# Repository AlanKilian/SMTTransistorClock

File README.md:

# SMTTransistorClock
Project files for a hand-built SMT transistor digital clock.

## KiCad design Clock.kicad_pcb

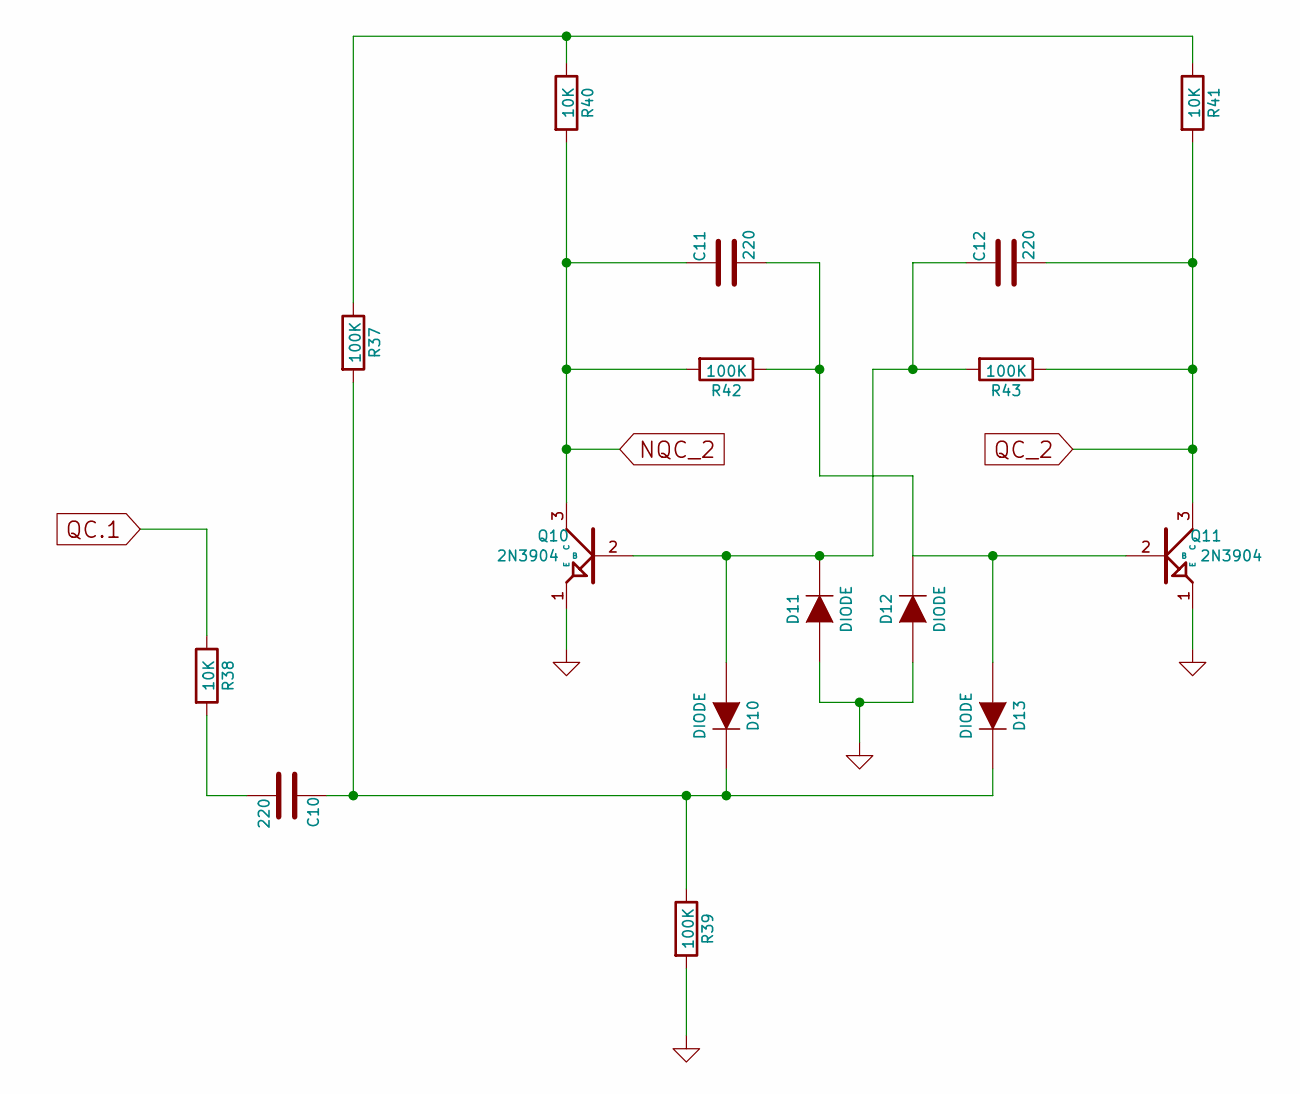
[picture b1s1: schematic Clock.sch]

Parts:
C10, C11, C12: 220; C_0805
D10, D11, D12, D13: DIODE; C_0805
Q10, Q11: 2N3904; sc70
R37, R39, R42, R43: 100K; R_0805
R38, R40, R41: 10K; R_0805

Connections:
GND: D11.1 (A), D12.1 (A), Q10.1 (E), Q11.1 (E), R39.2
NQC_2: C11.1, Q10.3 (C), R40.2, R42.2
unnamed: C10.1, D10.2 (K), D13.2 (K), R37.2, R39.1
unnamed: C10.2, R38.2
unnamed: C11.2, D12.2 (K), D13.1 (A), Q11.2 (B), R42.1
unnamed: C12.1, D10.1 (A), D11.2 (K), Q10.2 (B), R43.2
unnamed: R37.1, R40.1, R41.1
QC.1: R38.1
QC_2: C12.2, Q11.3 (C), R41.2, R43.1

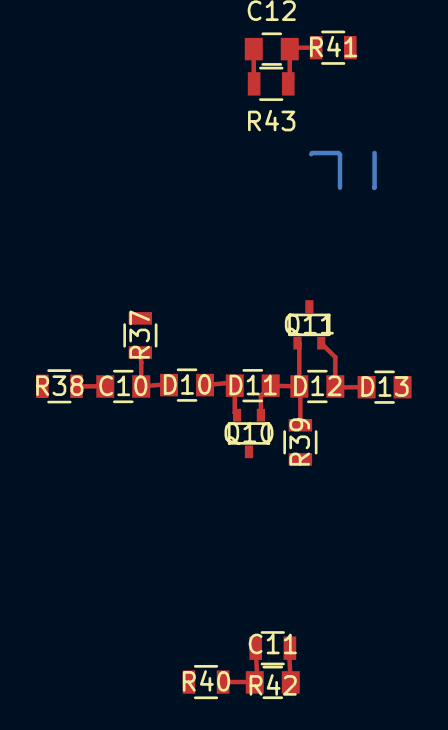
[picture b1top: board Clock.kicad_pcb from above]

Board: 2 copper layers, 16 parts (0 on the bottom side), 8 nets.

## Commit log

2015-07-05 Initial checkin. One FlipFlop schematic and PCB layout
